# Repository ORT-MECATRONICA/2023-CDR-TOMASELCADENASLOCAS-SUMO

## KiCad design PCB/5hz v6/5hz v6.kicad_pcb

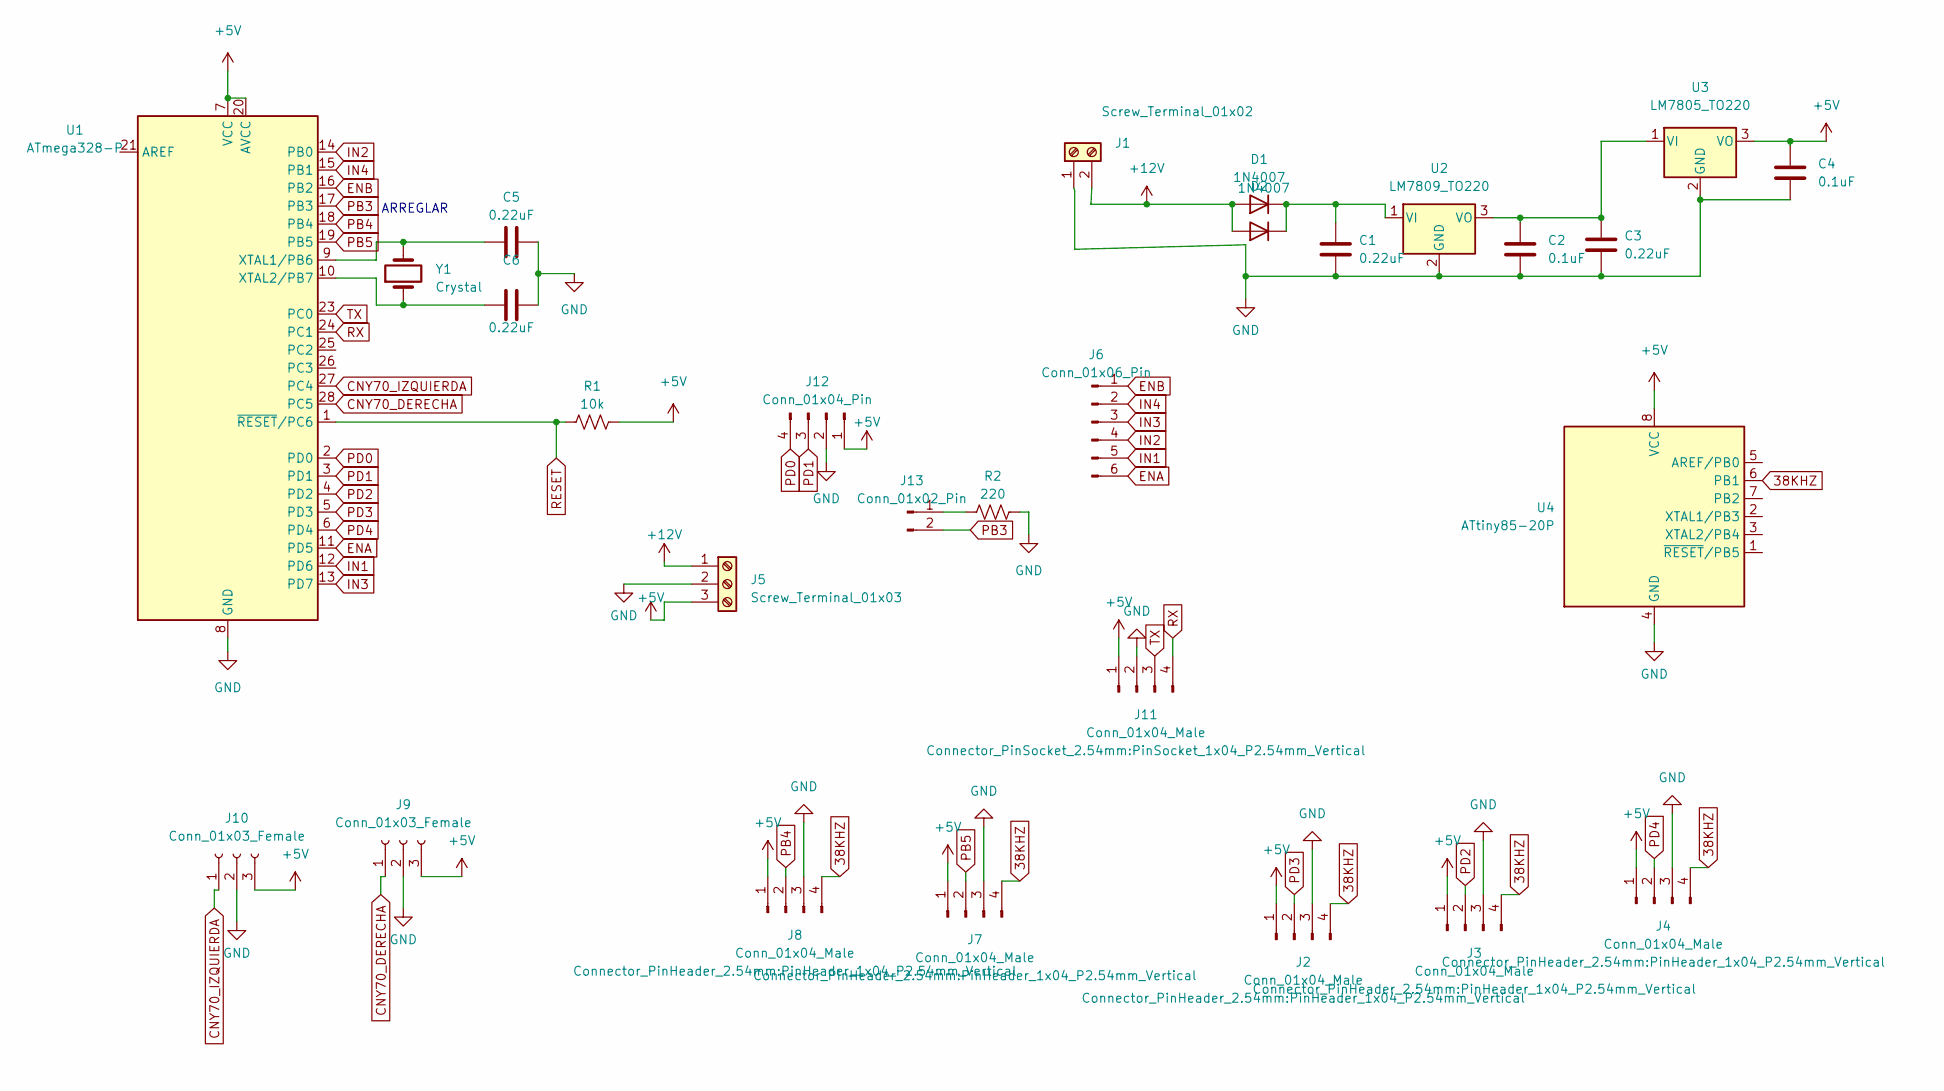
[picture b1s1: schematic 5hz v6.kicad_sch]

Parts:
C1, C3, C5, C6: 0.22uF; C_Disc_D4.3mm_W1.9mm_P5.00mm
C2, C4: 0.1uF; C_Disc_D4.3mm_W1.9mm_P5.00mm
D1, D2: 1N4007; D_DO-41_SOD81_P5.08mm_Vertical_KathodeUp
J1: Screw_Terminal_01x02; TerminalBlock_bornier-2_P5.08mm
J2, J3, J4, J7, J8: Conn_01x04_Male; PinHeader_1x04_P2.54mm_Vertical
J5: Screw_Terminal_01x03; TerminalBlock_bornier-3_P5.08mm
J6: Conn_01x06_Pin; PinHeader_1x06_P2.54mm_Horizontal
J9, J10: Conn_01x03_Female; PinSocket_1x03_P2.54mm_Horizontal
J11: Conn_01x04_Male; PinSocket_1x04_P2.54mm_Vertical
J12: Conn_01x04_Pin; PinHeader_1x04_P2.54mm_Vertical
J13: Conn_01x02_Pin; PinHeader_1x02_P2.54mm_Vertical
R1: 10k; R_Axial_DIN0204_L3.6mm_D1.6mm_P1.90mm_Vertical
R2: 220; R_Axial_DIN0204_L3.6mm_D1.6mm_P7.62mm_Horizontal
U1: ATmega328-P; DIP-28_W7.62mm
U2: LM7809_TO220; TO-220-3_Vertical
U3: LM7805_TO220; TO-220-3_Vertical
U4: ATtiny85-20P; DIP-8_W7.62mm
Y1: Crystal; Crystal_HC18-U_Vertical

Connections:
38KHZ: J2.4, J3.4, J4.4, J7.4, J8.4, U4.6 (PB1)
+5V: C4.2, J2.1, J3.1, J4.1, J5.3, J7.1, J8.1, J9.3, J10.3, J11.1, J12.1, R1.2, U1.7 (VCC), U1.20 (AVCC), U3.3 (VO), U4.8 (VCC)
+12V: D1.2 (A), D2.2 (A), J1.2, J5.1
CNY70_DERECHA: J9.1, U1.28 (PC5)
CNY70_IZQUIERDA: J10.1, U1.27 (PC4)
ENA: J6.6, U1.11 (PD5)
ENB: J6.1, U1.16 (PB2)
GND: C1.1, C2.1, C3.1, C4.1, C5.1, C6.1, J1.1, J2.3, J3.3, J4.3, J5.2, J7.3, J8.3, J9.2, J10.2, J11.2, J12.2, R2.2, U1.8 (GND), U1.22 (GND), U2.2 (GND), U3.2 (GND), U4.4 (GND)
IN1: J6.5, U1.12 (PD6)
IN2: J6.4, U1.14 (PB0)
IN3: J6.3, U1.13 (PD7)
IN4: J6.2, U1.15 (PB1)
unnamed: C1.2, D1.1 (K), D2.1 (K), U2.1 (VI)
unnamed: J13.1, R2.1
unnamed: C5.2, U1.9 (XTAL1/PB6), Y1.2
unnamed: C6.2, U1.10 (XTAL2/PB7), Y1.1
unnamed: C2.2, C3.2, U2.3 (VO), U3.1 (VI)
PB3: J13.2, U1.17 (PB3)
PB4: J8.2, U1.18 (PB4)
PB5: J7.2, U1.19 (PB5)
PD0: J12.4, U1.2 (PD0)
PD1: J12.3, U1.3 (PD1)
PD2: J3.2, U1.4 (PD2)
PD3: J2.2, U1.5 (PD3)
PD4: J4.2, U1.6 (PD4)
RESET: R1.1, U1.1 (~RESET/PC6)
RX: J11.4, U1.24 (PC1)
TX: J11.3, U1.23 (PC0)

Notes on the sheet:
ARREGLAR

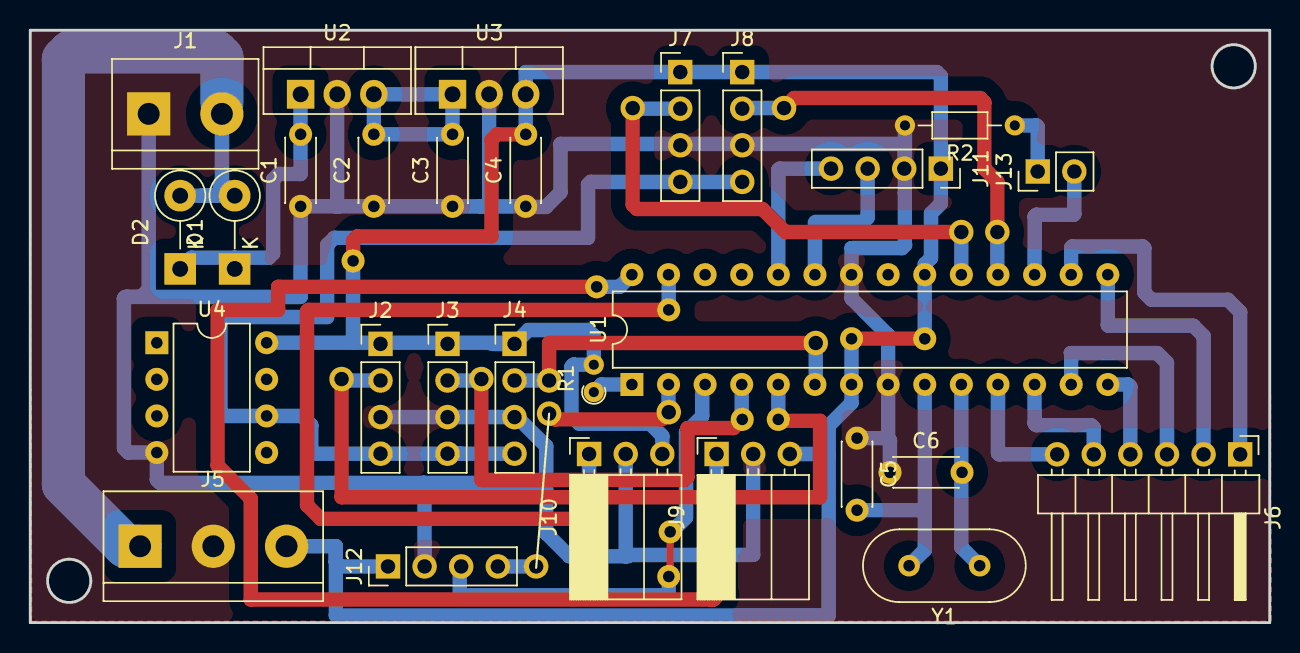
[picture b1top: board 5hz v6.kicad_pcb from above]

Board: 2 copper layers, 86.0 x 41.1 mm, 28 parts (0 on the bottom side), 28 nets.

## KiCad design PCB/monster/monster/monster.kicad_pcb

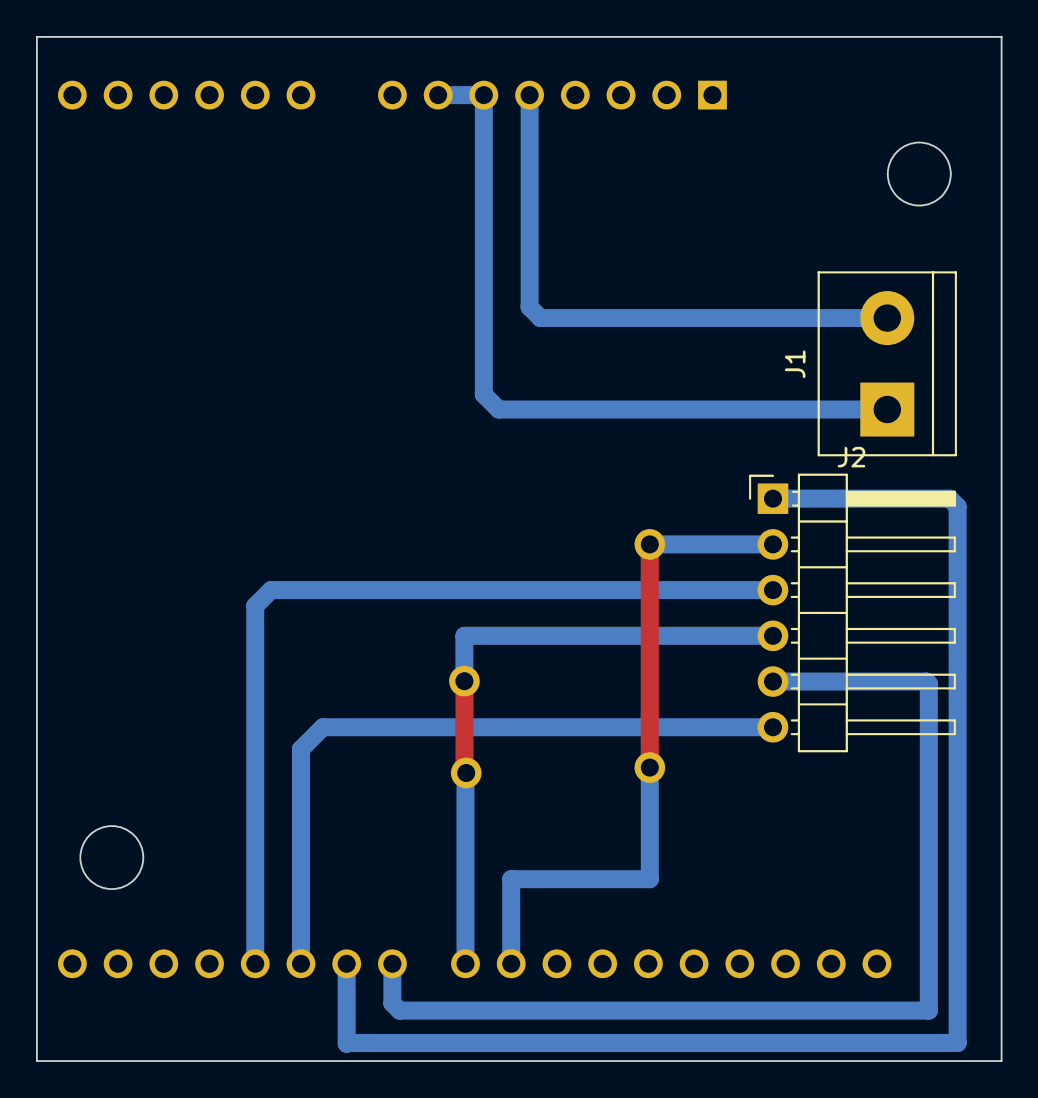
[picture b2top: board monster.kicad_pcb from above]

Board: 2 copper layers, 53.6 x 56.9 mm, 3 parts (1 on the bottom side), 8 nets.

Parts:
A1: VNH2SP30 MONSTER SHIELD; Arduino_UNO_R3
J1: Screw_Terminal_01x02; TerminalBlock_bornier-2_P5.08mm
J2: Conn_01x06_Pin; PinHeader_1x06_P2.54mm_Horizontal

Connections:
+5V: A1.5 (+5V), J1.2
ENA: A1.20 (ENA), J2.6
ENB: A1.21 (ENB), J2.1
GND: A1.6 (GND), A1.7 (GND), A1.29 (GND), J1.1
IN1: A1.22 (IN1), J2.5
IN2: A1.23 (IN2), J2.4
IN3: A1.19 (IN3), J2.3
IN4: A1.24 (IN4), J2.2

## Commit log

2023-09-27 placas de 5hz
2023-09-27 Codigo wanchope terminado
2023-09-28 motores y sensores andando
2023-09-28 codigo andando falta cny
